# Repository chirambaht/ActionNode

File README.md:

# Action Tracer Node
This repository supports the Action Tracer project which I undertook as part of my Masters Dissertation at the University of Cape Town in 2021 - 2022.

## What is Action Tracer?
This project aims to create a motion capture system based on the MPU-6050 IMU. This system is powered by a Raspberry Pi Zero W, which collects, processes and sends data, in real time, to a users device. 

Action Tracer differs from most systes due to its use of a 6-axes IMU and it's promise to deliver 30 frames per second with minimal latency over a Wi-Fi network. 

To see more on this project, please visit the main repository: [Action Tracer](https://github.com/chirambaht/Action-Tracer).
## Why a node?
To monitor each articulating joint, an IMU needs to be placed near by to capture its rotation. To help this, the design houses two 20mm wide slots that allow a strap to go through it and strap it to the area it is montoring. At this stage, this design shows a wired node but future plans involve turning this node wireless. One such implementation of this was attempted and can be found here: [Wireless Action Node](https://github.com/chirambaht/WirelessAction).
## Bill of Materials
| Comment     | Designator | Footprint                      | LCSC   |
|-------------|------------|--------------------------------|--------|
| 0.1u        | C2,C5      | C_0603_1608Metric              | C14663 |
| 2.2n        | C3         | C_0603_1608Metric              | C1604  |
| 0.33u       | C4         | C_0603_1608Metric              | C1615  |
| Power       | D1,D2      | LED_0603_1608Metric            | C2286  |
| MPU-6050    | U1         | InvenSense_QFN-24_4x4mm_P0.5mm | C24112 |
| 10k         | R1,R2      | R_0603_1608Metric              | C25804 |
| 68          | R3,R4      | R_0603_1608Metric              | C27592 |
| 10n         | C1         | C_0603_1608Metric              | C57112 |
| AMS1117-3.3 | U2         | SOT-223-3_TabPin2              | C6186  |
## Images

A picture showing the front of the board. This will hold all the components used in this project. 

The rear side of the board with markings for each of the connector lines, showing where they should be placed.
## Tools
This board was designed in KiCad 6.0.

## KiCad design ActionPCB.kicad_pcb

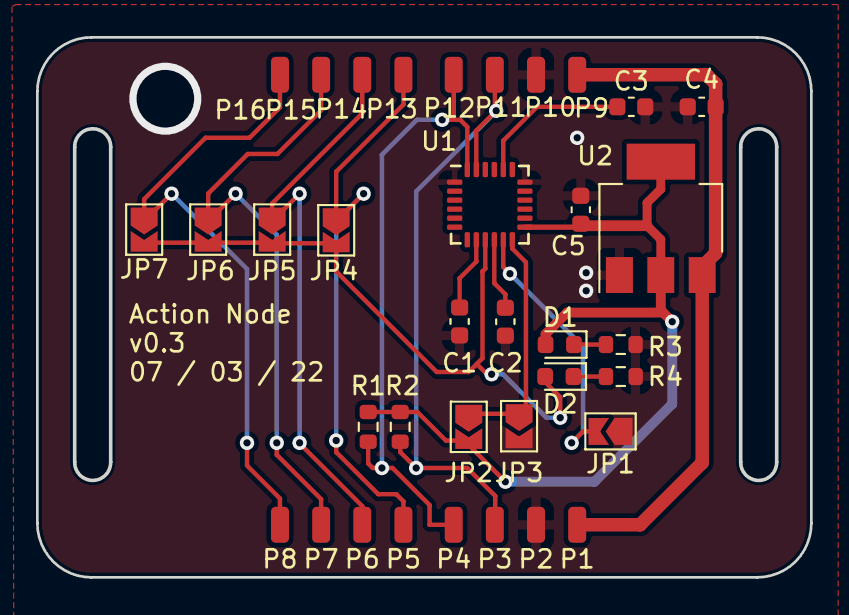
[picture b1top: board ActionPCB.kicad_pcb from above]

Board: 2 copper layers, 42.9 x 30.0 mm, 36 parts (0 on the bottom side), 17 nets.

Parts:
C1: 10n; C_0603_1608Metric
C2, C5: 0.1u; C_0603_1608Metric
C3: 2.2n; C_0603_1608Metric
C4: 0.33u; C_0603_1608Metric
D1: Power; LED_0603_1608Metric
D2: Selector; LED_0603_1608Metric
JP1, JP2, JP3, JP4, JP5, JP6, JP7: Jumper; SolderJumper-2_P1.3mm_Open_TrianglePad1.0x1.5mm
P1, P9: VCC; SolderWirePad_1x01_SMD_1x2mm
P2, P10: GND; SolderWirePad_1x01_SMD_1x2mm
P3, P11: SCL; SolderWirePad_1x01_SMD_1x2mm
P4, P12: SDA; SolderWirePad_1x01_SMD_1x2mm
P5, P13: CH1; SolderWirePad_1x01_SMD_1x2mm
P6, P14: CH2; SolderWirePad_1x01_SMD_1x2mm
P7, P15: CH3; SolderWirePad_1x01_SMD_1x2mm
P8, P16: CH4; SolderWirePad_1x01_SMD_1x2mm
R1, R2: 10k; R_0603_1608Metric
R3, R4: 68; R_0603_1608Metric
U1: MPU-6050; InvenSense_QFN-24_4x4mm_P0.5mm
U2: AMS1117-3.3; SOT-223-3_TabPin2

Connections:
+3V3: C5.1, D1.2 (A), JP2.2 (B), R1.1, R2.1, U1.13 (VDD), U2.2 (VO)
/AD0: D2.2 (A), JP4.2 (B), JP5.2 (B), JP6.2 (B), JP7.2 (B), U1.9 (AD0)
/CH1: JP4.1 (A), P5.1, P13.1
/CH2: JP5.1 (A), P6.1, P14.1
/CH3: JP6.1 (A), P7.1, P15.1
/CH4: JP7.1 (A), P8.1, P16.1
/INT: JP2.1 (A), JP3.1 (A), U1.12 (INT)
/SCL: P3.1, P11.1, R2.2, U1.23 (SCL)
/SDA: P4.1, P12.1, R1.2, U1.24 (SDA)
GND: C1.2, C2.2, C3.2, C4.2, C5.2, JP1.1 (A), JP3.2 (B), P2.1, P10.1, R3.1, R4.1, U1.1 (CLKIN), U1.18 (GND), U2.1 (GND)
unnamed: C1.1, U1.8 (VDDIO)
unnamed: C2.1, U1.10 (REGOUT)
unnamed: C3.1, U1.20 (CPOUT)
unnamed: D1.1 (K), R3.2
unnamed: D2.1 (K), R4.2
unnamed: JP1.2 (B), U1.11 (FSYNC)
VCC: C4.1, P1.1, P9.1, U2.3 (VI)

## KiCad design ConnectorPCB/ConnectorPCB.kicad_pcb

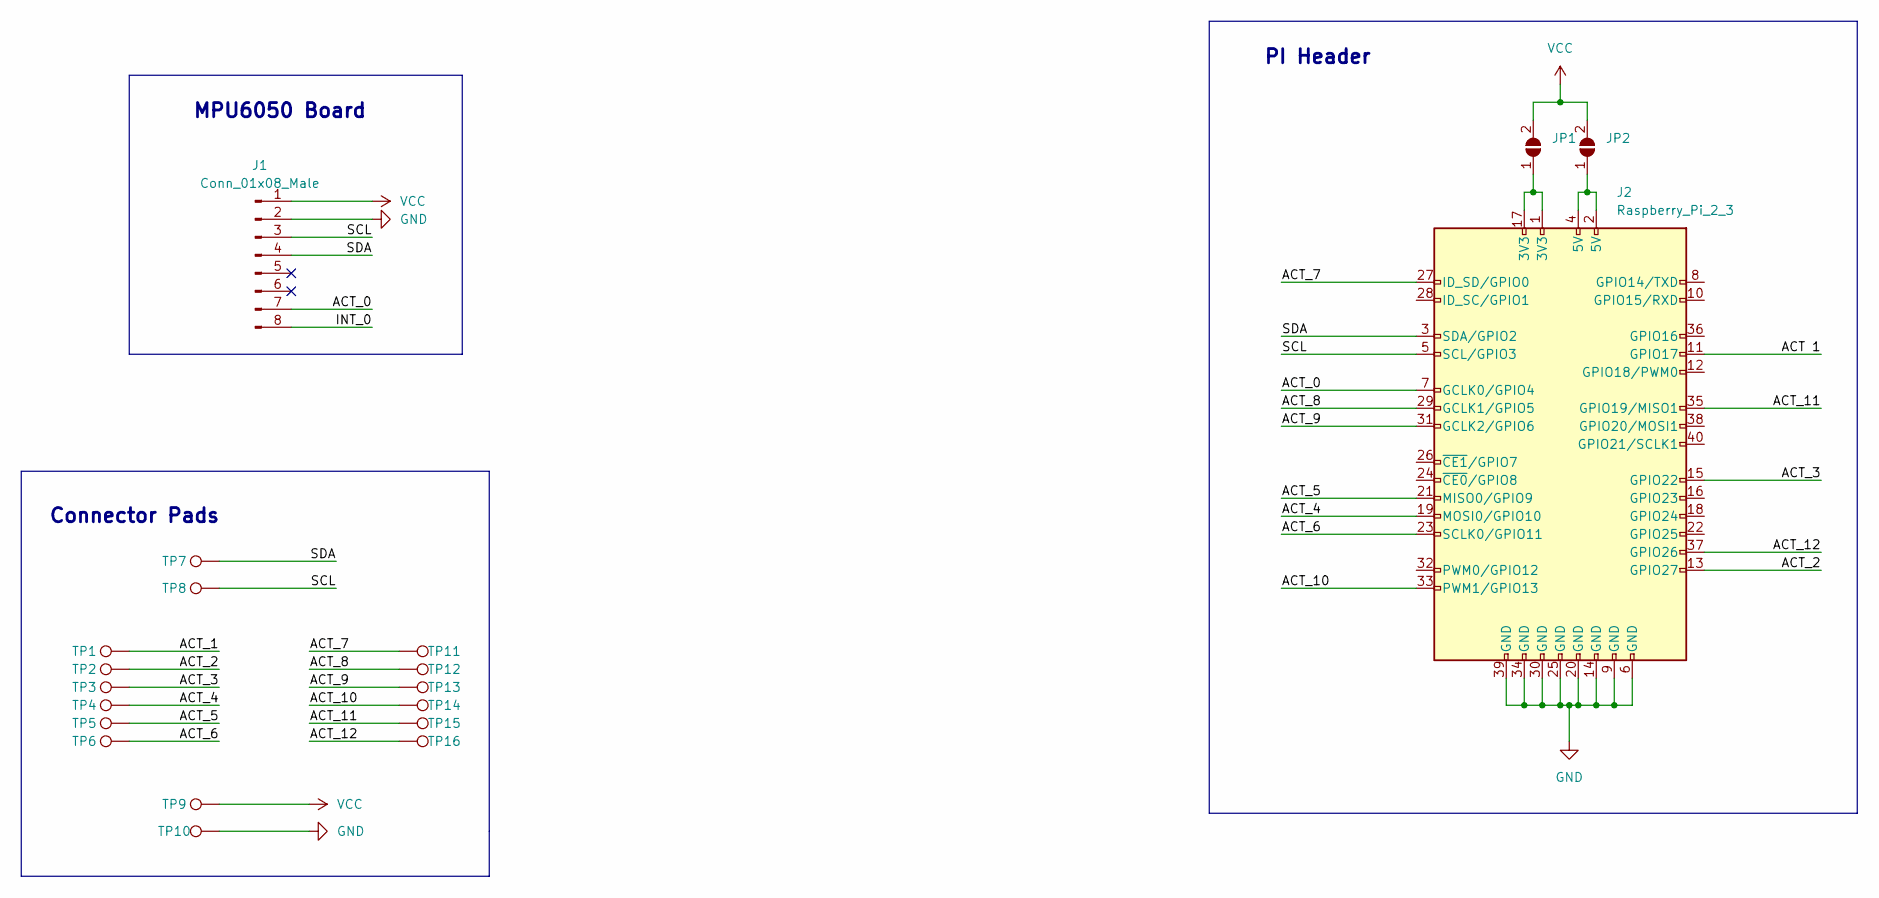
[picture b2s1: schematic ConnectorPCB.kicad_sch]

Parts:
J1: Conn_01x08_Male; PinSocket_1x08_P2.54mm_Vertical
J2: Raspberry_Pi_2_3; Raspberry_Pi_Zero_Socketed_THT_FaceDown_MountingHoles
JP1, JP2: SolderJumper_2_Open; SolderJumper-2_P1.3mm_Open_TrianglePad1.0x1.5mm
TP1, TP2, TP3, TP4, TP5, TP6, TP7, TP8, TP9, TP10, TP11, TP12, TP13, TP14, TP15, TP16: TestPoint; SolderWirePad_1x01_SMD_1x2mm

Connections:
/ACT_0: J1.7, J2.7 (GCLK0/GPIO4)
/ACT_2: J2.13 (GPIO27), TP2.1
/ACT_3: J2.15 (GPIO22), TP3.1
/ACT_4: J2.19 (MOSI0/GPIO10), TP4.1
/ACT_5: J2.21 (MISO0/GPIO9), TP5.1
/ACT_6: J2.23 (SCLK0/GPIO11), TP6.1
/ACT_7: J2.27 (ID_SD/GPIO0), TP11.1
/ACT_8: J2.29 (GCLK1/GPIO5), TP12.1
/ACT_9: J2.31 (GCLK2/GPIO6), TP13.1
/ACT_10: J2.33 (PWM1/GPIO13), TP14.1
/ACT_11: J2.35 (GPIO19/MISO1), TP15.1
/ACT_12: J2.37 (GPIO26), TP16.1
/INT_0: J1.8
/SCL: J1.3, J2.5 (SCL/GPIO3), TP8.1
/SDA: J1.4, J2.3 (SDA/GPIO2), TP7.1
GND: J1.2, J2.6 (GND), J2.9 (GND), J2.14 (GND), J2.20 (GND), J2.25 (GND), J2.30 (GND), J2.34 (GND), J2.39 (GND), TP10.1
unnamed: J2.1 (3V3), J2.17 (3V3), JP1.1 (A)
unnamed: J2.2 (5V), J2.4 (5V), JP2.1 (A)
VCC: J1.1, JP1.2 (B), JP2.2 (B), TP9.1

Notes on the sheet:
MPU6050 Board
Connector Pads
PI Header

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
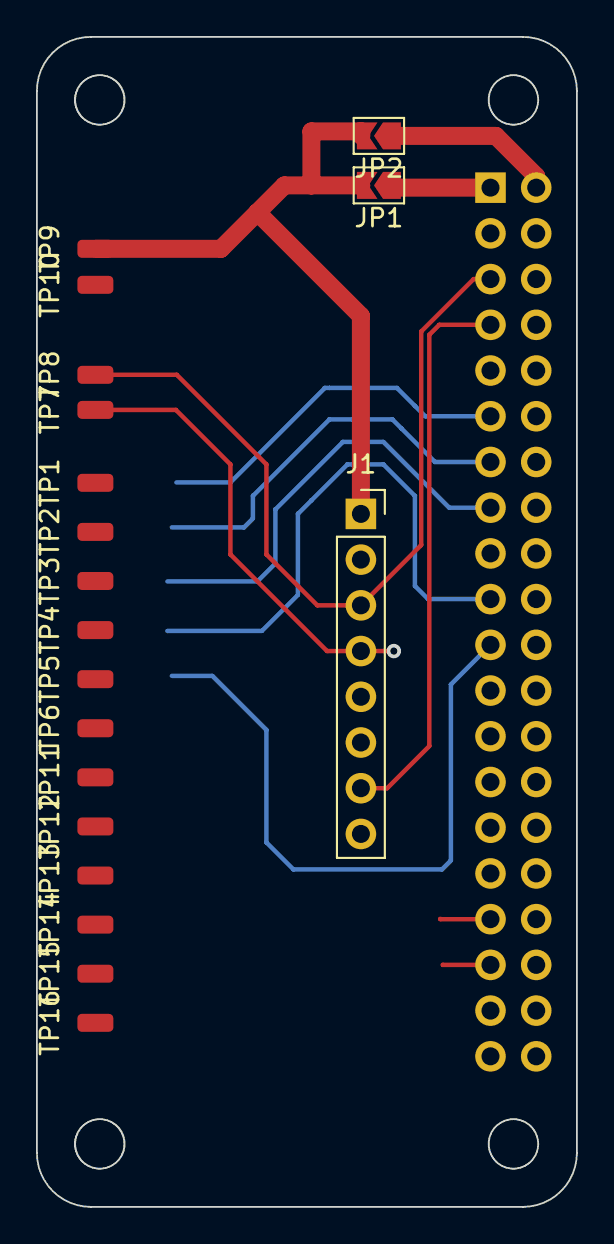
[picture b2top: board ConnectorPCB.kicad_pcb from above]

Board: 2 copper layers, 30.0 x 65.0 mm, 20 parts (1 on the bottom side), 19 nets.

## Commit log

2022-03-07 Almost complete
2022-03-07 Final board single
2022-03-07 Ready for panelization
2022-03-15 Completed pricy board
2022-03-19 Everything
2022-03-19 Pi connector PCB added
2022-11-15 Updated repo documentation
